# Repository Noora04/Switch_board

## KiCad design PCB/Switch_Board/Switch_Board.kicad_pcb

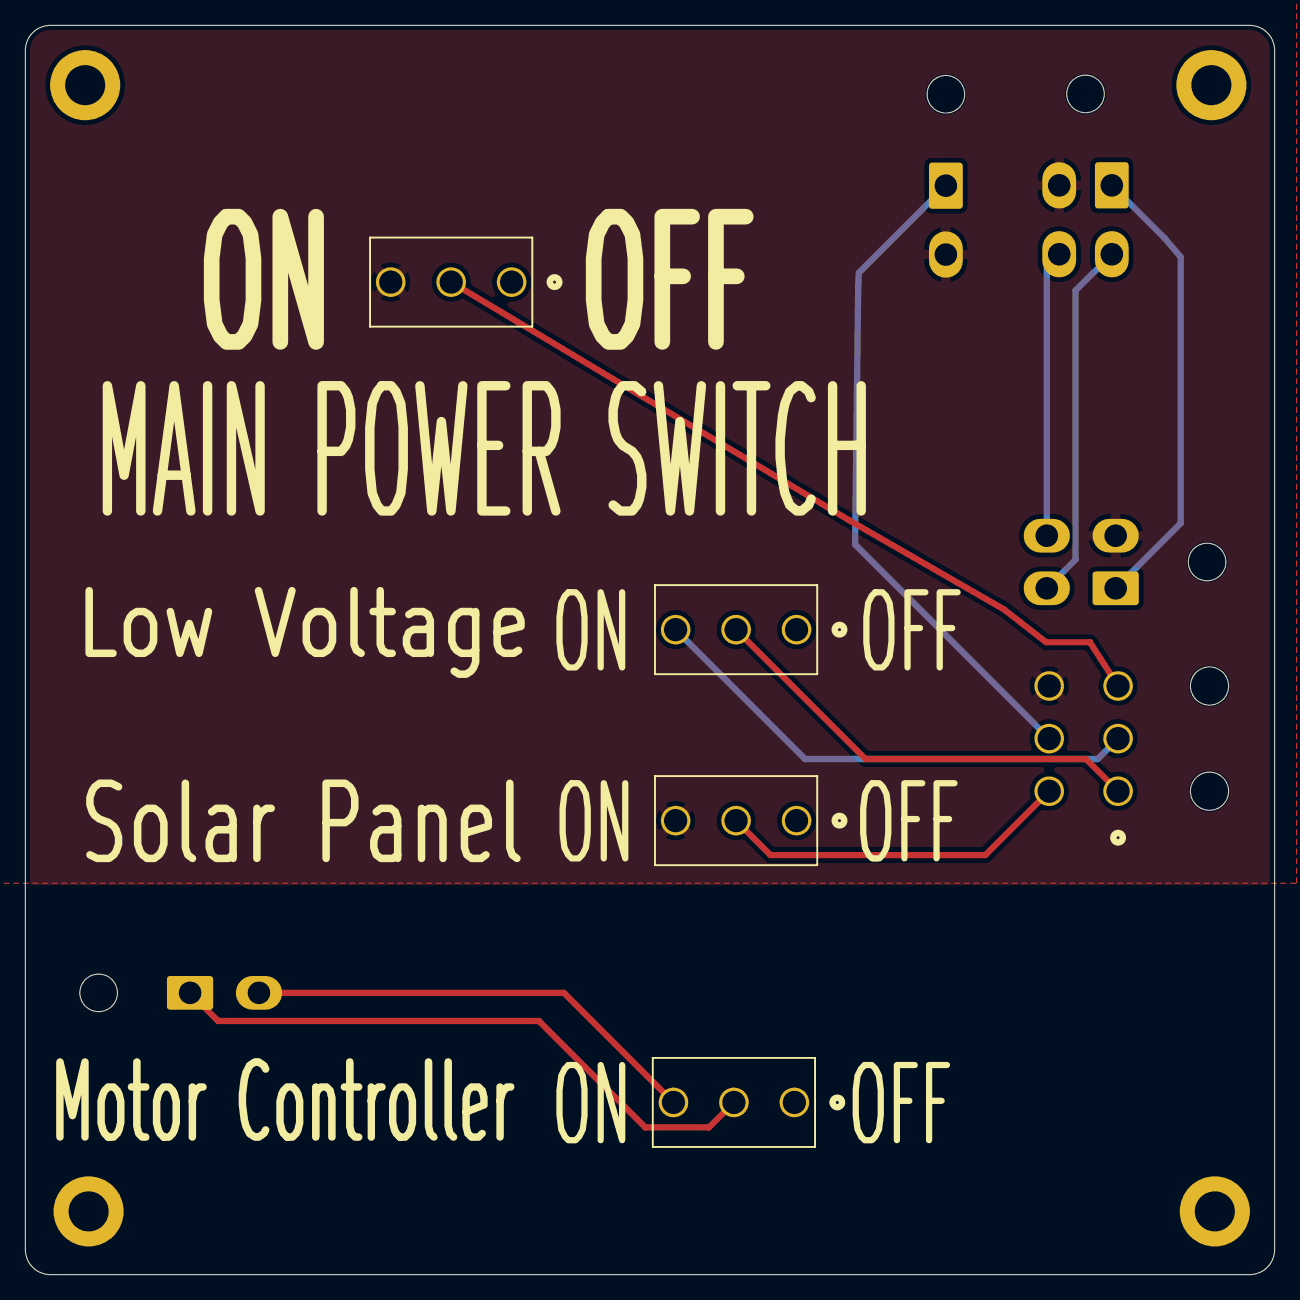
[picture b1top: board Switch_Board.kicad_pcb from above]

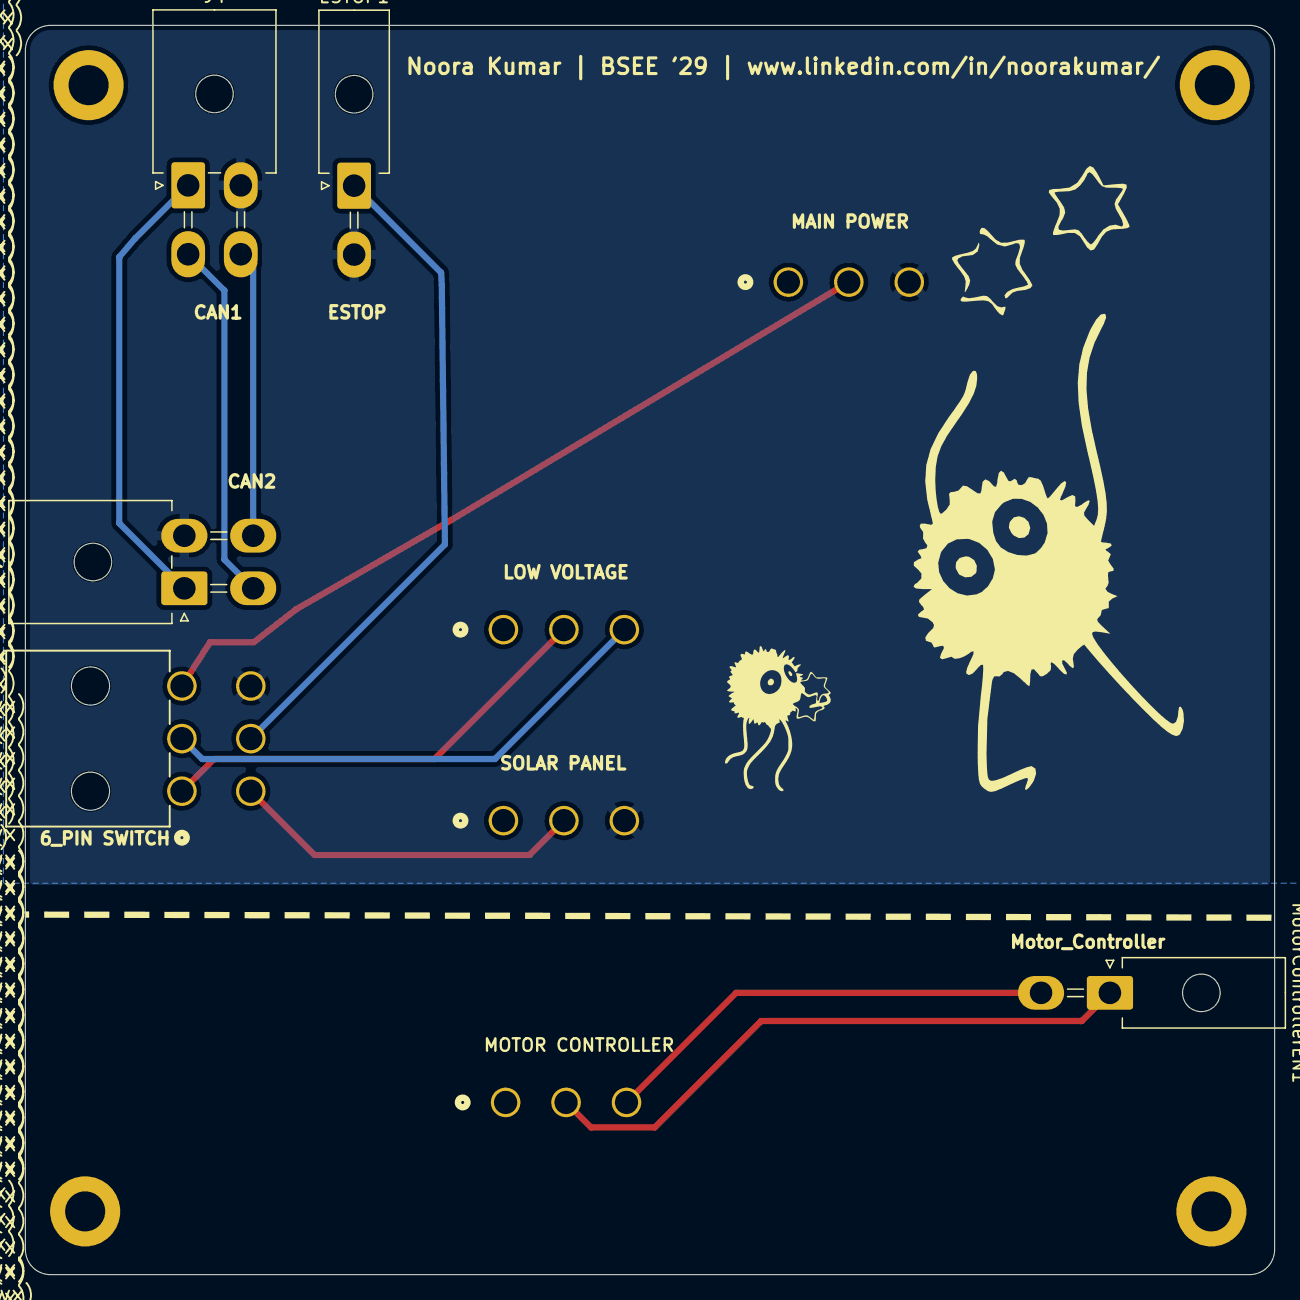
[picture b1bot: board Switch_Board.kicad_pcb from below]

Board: 2 copper layers, 99.8 x 99.8 mm, 9 parts (5 on the bottom side), 11 nets.

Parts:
ESTOP1: Conn_01x02; Molex_Mini-Fit_Jr_5569-02A2_2x01_P4.20mm_Horizontal
HV1: SW_Nidec_CAS-120A1; ANT13SEC_CRS
J1, J4: Conn_01x04_Pin; Molex_Mini-Fit_Jr_5569-04A2_2x02_P4.20mm_Horizontal
LV1: SW_Nidec_CAS-120A1; ANT13SEC_CRS
MotorController1: SW_Nidec_CAS-120A1; ANT13SEC_CRS
MotorControllerEN1: Conn_01x02; Molex_Mini-Fit_Jr_5569-02A2_2x01_P4.20mm_Horizontal
SolarPanel1: SW_Nidec_CAS-120A1; ANT13SEC_CRS
Switch1: CONN_5569-06A_MOL

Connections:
+12V: J1.1, J4.1
/CANH1: J1.3, J4.3
/CANL1: J1.4, J4.4
/ESTOP: ESTOP1.1, Switch1.5
/HV_EN: HV1.2 (B), Switch1.3
/LV_EN_PWR: LV1.2 (B), Switch1.1
/LV_EN_SIGNAL: LV1.3 (A), Switch1.2
/Solar_EN: SolarPanel1.2 (B), Switch1.4
GND: ESTOP1.2, HV1.3 (A), J1.2, J4.2, SolarPanel1.3 (A), Switch1.6
unnamed: MotorController1.3 (A), MotorControllerEN1.2
unnamed: MotorController1.2 (B), MotorControllerEN1.1

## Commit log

2026-03-21 PCB Files Added
2026-04-13 Updated Version_04_13
2026-04-13 Change pinout to match BMS
2026-04-18 Updated_Final_0418
    Not including image yet, but it is the final board
2026-04-18 SpritesAdded_0418
2026-04-18 Updated_Images_Back_0418
2026-04-18 FINAL SWITCH BOARD
